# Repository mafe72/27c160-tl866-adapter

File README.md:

<div align="right">
  <details>
    <summary >🌐 Language</summary>
    <div>
      <div align="center">
        <a href="https://openaitx.github.io/view.html?user=mafe72&project=27c160-tl866-adapter&lang=en">English</a>
        | <a href="https://openaitx.github.io/view.html?user=mafe72&project=27c160-tl866-adapter&lang=zh-CN">简体中文</a>
        | <a href="https://openaitx.github.io/view.html?user=mafe72&project=27c160-tl866-adapter&lang=zh-TW">繁體中文</a>
        | <a href="https://openaitx.github.io/view.html?user=mafe72&project=27c160-tl866-adapter&lang=ja">日本語</a>
        | <a href="https://openaitx.github.io/view.html?user=mafe72&project=27c160-tl866-adapter&lang=ko">한국어</a>
        | <a href="https://openaitx.github.io/view.html?user=mafe72&project=27c160-tl866-adapter&lang=hi">हिन्दी</a>
        | <a href="https://openaitx.github.io/view.html?user=mafe72&project=27c160-tl866-adapter&lang=th">ไทย</a>
        | <a href="https://openaitx.github.io/view.html?user=mafe72&project=27c160-tl866-adapter&lang=fr">Français</a>
        | <a href="https://openaitx.github.io/view.html?user=mafe72&project=27c160-tl866-adapter&lang=de">Deutsch</a>
        | <a href="https://openaitx.github.io/view.html?user=mafe72&project=27c160-tl866-adapter&lang=es">Español</a>
        | <a href="https://openaitx.github.io/view.html?user=mafe72&project=27c160-tl866-adapter&lang=it">Italiano</a>
        | <a href="https://openaitx.github.io/view.html?user=mafe72&project=27c160-tl866-adapter&lang=ru">Русский</a>
        | <a href="https://openaitx.github.io/view.html?user=mafe72&project=27c160-tl866-adapter&lang=pt">Português</a>
        | <a href="https://openaitx.github.io/view.html?user=mafe72&project=27c160-tl866-adapter&lang=nl">Nederlands</a>
        | <a href="https://openaitx.github.io/view.html?user=mafe72&project=27c160-tl866-adapter&lang=pl">Polski</a>
        | <a href="https://openaitx.github.io/view.html?user=mafe72&project=27c160-tl866-adapter&lang=ar">العربية</a>
        | <a href="https://openaitx.github.io/view.html?user=mafe72&project=27c160-tl866-adapter&lang=fa">فارسی</a>
        | <a href="https://openaitx.github.io/view.html?user=mafe72&project=27c160-tl866-adapter&lang=tr">Türkçe</a>
        | <a href="https://openaitx.github.io/view.html?user=mafe72&project=27c160-tl866-adapter&lang=vi">Tiếng Việt</a>
        | <a href="https://openaitx.github.io/view.html?user=mafe72&project=27c160-tl866-adapter&lang=id">Bahasa Indonesia</a>
        | <a href="https://openaitx.github.io/view.html?user=mafe72&project=27c160-tl866-adapter&lang=as">অসমীয়া</
      </div>
    </div>
  </details>
</div>

# 27C322/160/800/400 EPROM Programming Adapter Series

## Introduction

This adapter converts the pin-outs of the parts listed below (which are similar to contemporary DIP-packaged mask ROMs) to 27C4096 pin-out as supported by the readily-available and cheap TL866 series of USB programmers.

The supported EPROMs parts are:
- **27C400:** 40-pin, 4Mbit (256k x 16-bit, 512k x 8-bit)
- **27C800:** 42-pin, 8Mbit (512k x 16-bit, 1M x 8-bit)
- **27C160:** 42-pin, 16Mbit (1M x 16-bit, 2M x 8-bit)
- **27C322:** 42-pin, 32Mbit (2M x 16-bit, no 8-bit access mode)

## Design

This adapter was designed using KiCad 5.0, you can find the project files on the folder called kicad-project.

Top Side:

Bottom Side:

## Usage

Insert the programming adapter into the TL866 with the socket handles adjacent to each other. Insert the EPROM into the lowest-possible position in the adapter and with pin 1 nearest the handle.

If your are programming a 27C322 EPROMs, move the switch to the **Position 27c322**, for 27C160 , 27C400 and 27C800 EPROMs, switch must be in the **Position other**.

## Software

The following instructions describe how to write a 27c160 EPROM.

Split the source EPROM into 512Kbytes parts, in this case I use the HJSplit, however other programs can be used.

Located the output path, for this example four files of 512Kbyte size with the extension ending on ".001" - ".004".

Launch the MiniPro software, select `AMD 27C4096 DIP40` device, deselect `Check ID` and set `Pulse Delay` to `50us`. You may also optionally reduce `VPP Voltage` to `12.50V`, depending on your EPROM's datasheet and programming success.

The EPROM can now be accessed as if it were a 27C4096 device, 512kB at a time, as configured by the DIP Switch:

- **27C400:** program all 512kB in one pass.
- **27C800:** program in 2 (two) 512kB passes.
- **27C160:** program in 4 (four) 512kB passes.
- **27C322:** program in 8 (eight) 512kB passes.

Refer to the following table for DIP Switch configuration:

## Troubleshooting

If you suffer write or verify errors when programming, try these steps:

1. Make sure the EPROM is fully blank before programming it (`Device -> Blank Check`). All EPROMs available today are second-hand 'pulls'; sellers aren't always careful when erasing before resale.

2. Open and close the adapter's ZIF lever a few times, and reposition the EPROM squarely in the socket.

3. Try adjusting `VPP Voltage` between `12.50V` and `13.50V`. Subjectively, I have had greater success at the higher voltage, which gives headroom for voltage losses in transferring VPP through the adapter's logic.

4. Programming errors will occur occasionally, and of course, the chances increase the larger the device. It makes sense to invest in a UV eraser. These are available at a low cost on eBay for around $15-20. Most devices will be erased after 10 to 20 minutes under UV light.

5. [Maillouski](https://github.com/Maillouski/), reported that Xgpro v12.38 sets the default VDD Write value to 6.60V for the AT27C4096. To avoid programming issues, make sure you change this value to 3.30V.

6. [Tim aka BeepFixer](https://x.com/@beepfixer), shares his programming values for the **27C160** variants sourced from AliExpress.

   The main difference: the UV window pad configuration. call them Types A, B, and C.
    - **Type A**: 2x2 pads using only the center of the available window space 
    - **Type B**: 2x2 pads using most of the available window space 
    - **Type C**: 2x4 pads

**Testing Results**

  **Type A**: 2/10 chips needed a little TLC-a tiny tweak outside recommended settings (changing 50us 100us) made them programmable and verifiable. Just to be sure, here's the full settings used: VPP Voltage: 13.50V / VCC Verify:. 5.00V / VDD Write: 5.00V / Puls Delay: 100us. Although did have success with other voltages too, as long as the Puls Delay was at 100 and not 50us.

  **Type B**: 7/10 chips worked flawlessly- first try, recommended settings from Eladio (50us)

  **Type C**: 1/10 chip failed spectacularly. It reads and erases just fine, and can write a single word. But after the single word right it refuses to write more than that. Likely an older, stricter variant; not broken, just a silicon diva. I tried over and over again with different settings and can simply not get it to write a full batch. 

**Practical tips**

   - Always verify after programming. 
   - Try voltage differences as also mentioned in the adapter's GitHub.
   - And keep of file writes; since you will be using the adapter to write an image split into 4 sections, it is easy to write the wrong file to the wrong bank (oopsie, yes guilty of writing file 3 to bank 3 and 4 myself once). So, do verify the EPROM on the destination device!

## Hardware change log

R_20231123

* Fix EDG-03 DIP Switch's correct polarity.
* Update revision number to R_20231123
* Update Version number to 1.1

V_20180919

* Initial release.

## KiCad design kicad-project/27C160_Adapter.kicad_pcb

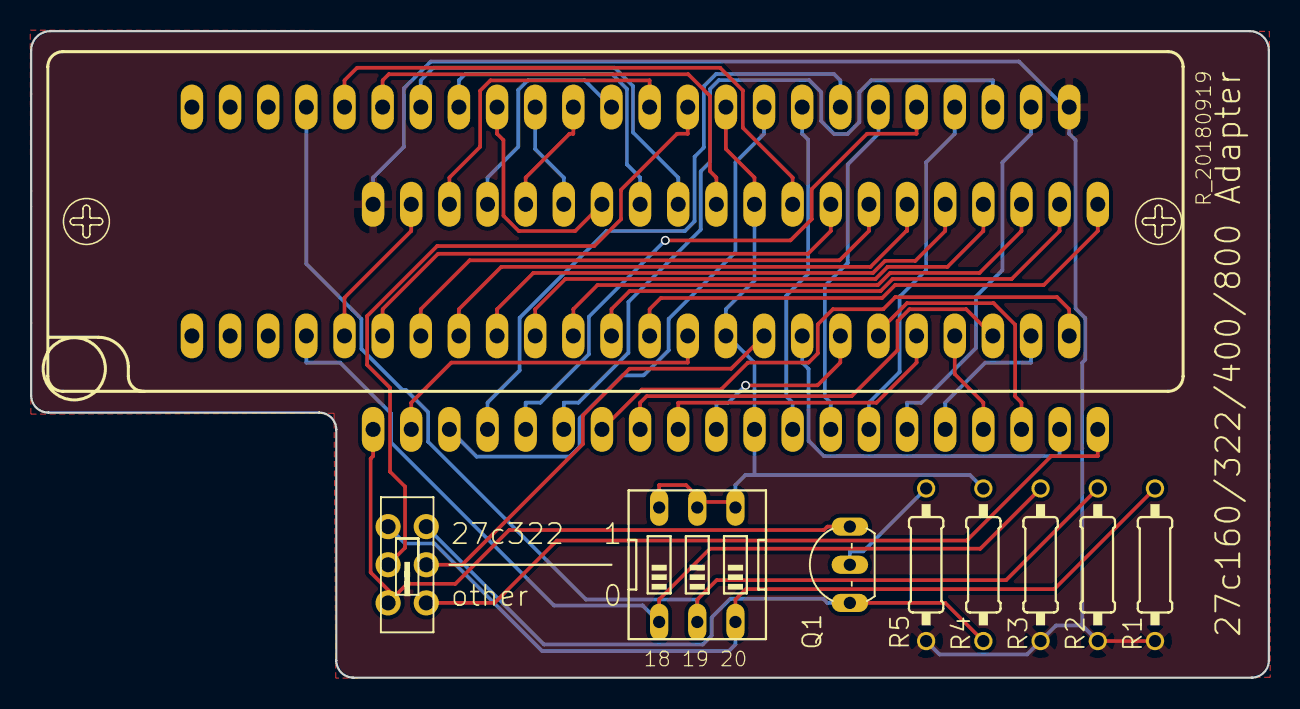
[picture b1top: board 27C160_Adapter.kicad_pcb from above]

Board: 2 copper layers, 82.4 x 43.1 mm, 12 parts (0 on the bottom side), 46 nets.

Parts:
G001: LOGO; mini-mods
Q1: BC327; TO92-EBC
R1, R2, R3, R4, R5: 10k; 0207%2f10
REF01: OSHW-Logo2_9.8x8mm_SilkScreen
SW1: MS22D16
SW2: DIP; EDG-03
U1: 27C4002
ZX1: 3M_248-3345

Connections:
/A0: U1.21, ZX1.13
/A1: U1.22, ZX1.12
/A2: U1.23, ZX1.11
/A3: U1.24, ZX1.10
/A4: U1.25, ZX1.9
/A5: U1.26, ZX1.8
/A6: U1.27, ZX1.7
/A7: U1.28, ZX1.6
/A8: U1.29, ZX1.44
/A9: U1.31, ZX1.43
/A10: U1.32, ZX1.42
/A11: U1.33, ZX1.41
/A12: U1.34, ZX1.40
/A13: U1.35, ZX1.39
/A14: U1.36, ZX1.38
/A15: U1.37, ZX1.37
/A16: U1.38, ZX1.36
/A17: U1.39, ZX1.5
/A18: R3.1, SW2.1, ZX1.4
/A19: R2.1, SW2.2, ZX1.45
/A20: R1.1, SW1.3, SW2.3
/D0: U1.19, ZX1.17
/D1: U1.18, ZX1.19
/D2: U1.17, ZX1.21
/D3: U1.16, ZX1.23
/D4: U1.15, ZX1.26
/D5: U1.14, ZX1.28
/D6: U1.13, ZX1.30
/D7: U1.12, ZX1.32
/D8: U1.10, ZX1.18
/D9: U1.9, ZX1.20
/D10: U1.8, ZX1.22
/D11: U1.7, ZX1.24
/D12: U1.6, ZX1.27
/D13: U1.5, ZX1.29
/D14: U1.4, ZX1.31
/D15: U1.3, ZX1.33
/E: U1.2, ZX1.14
/N$1: Q1.B, R5.2
/N$2: SW1.2, ZX1.35
/N$4: Q1.C, R4.2, SW1.6
/N$5: SW1.4, U1.20
/N$6: SW1.5, ZX1.16
/VPP: Q1.E, SW1.1, U1.1
GND: R4.1, SW2.4, SW2.5, SW2.6, U1.11, U1.30, ZX1.15, ZX1.34
VCC: R1.2, R2.2, R3.2, R5.1, U1.40, ZX1.25

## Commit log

2018-09-26 Adjust image margin
2021-06-11 Update images names
2021-06-11 Update software section
2021-06-11 Adjust image borders
2021-09-12 Update front and back images
2023-11-23 Fix EDG-03 DIP Switch's correct polarity
    R_20231123
    Fix EDG-03 DIP Switch's correct polarity.
    Uppdate revision number to R_20231123
    Update Version number to 1.1
2023-11-23 Create gerber
2023-11-23 Fix EDG-03 DIP Switch's correct polarity
    R_20231123
    Fix EDG-03 DIP Switch's correct polarity.
    Update revision number to R_20231123
    Update Version number to 1.1
2025-01-15 IC config VDD Write 3.30V
2025-01-15 Update troubleshooting section
    Correct VDD Write value for the Xgpro v12.38 provided by Nicolas Mailloux
2025-12-26 add m27c160 variants
    File provided by Tim aka BeepFixer
2025-12-29 Update README.md
    Add BeepFixer's 27C160 programming values to the Troubleshooting section
2025-12-29 Add BeepFixer's 27C160 programming values to the Troubleshooting section
2026-01-24 Auto-translate README and Wiki
